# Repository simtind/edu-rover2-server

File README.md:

# EduROV server package

This package contains a server for use with the [circuit boards](https://github.com/simtind/edu-rover2-pcb) and [PC client](https://github.com/simtind/edu-rover2-client) from the pyedurov2 project, and the ROV chassis described on the EduROV webpage.

## Use
- To install, run ```pip install pyedurov2```.
  - If you got the warning ```The script normalizer is installed in * which is not on PATH.```, call ```source ~/.profile```.
- To run the server, run ```pyedurov2```.
- To start the server at boot, run ```pyedurov2 --runatstartup```.
- See ```pyedurov2 --help``` foor more options.

## Building package

Make sure the newest version of pip is installed: ```pip install --upgrade build```
Then from the edurov_server folder, run ```python -m build```

## Setting up Raspberry pi for EduROV

- Install Raspberry PI OS (32-bit), for example via [Raspberry Pi Imager](https://www.raspberrypi.com/software/)
- In SD card, add the file "ssh", it should be empty.
- Insert sd card to raspberry pi
- Connect via ssh to raspberrypi.local
- Via raspi-config:
  - Under Interface Options
    - Enable camera
    - Enable Serial Port:
      - We do not want a login shell to be available.
      - We do want the serial port hardware to obe enabled.
  - Allow the raspberry pi to restart and reconnect the ssh session.
- For pyedurov2 to run at startup, we'll need to install and run it as sudo.
- Install pyedurov2 with ```sudo pip install pyedurov2```
- Call ```sudo pyedurov2 --runatstartup --name=yourname``` to set server to start at boot with "yourname" as the advertising name.

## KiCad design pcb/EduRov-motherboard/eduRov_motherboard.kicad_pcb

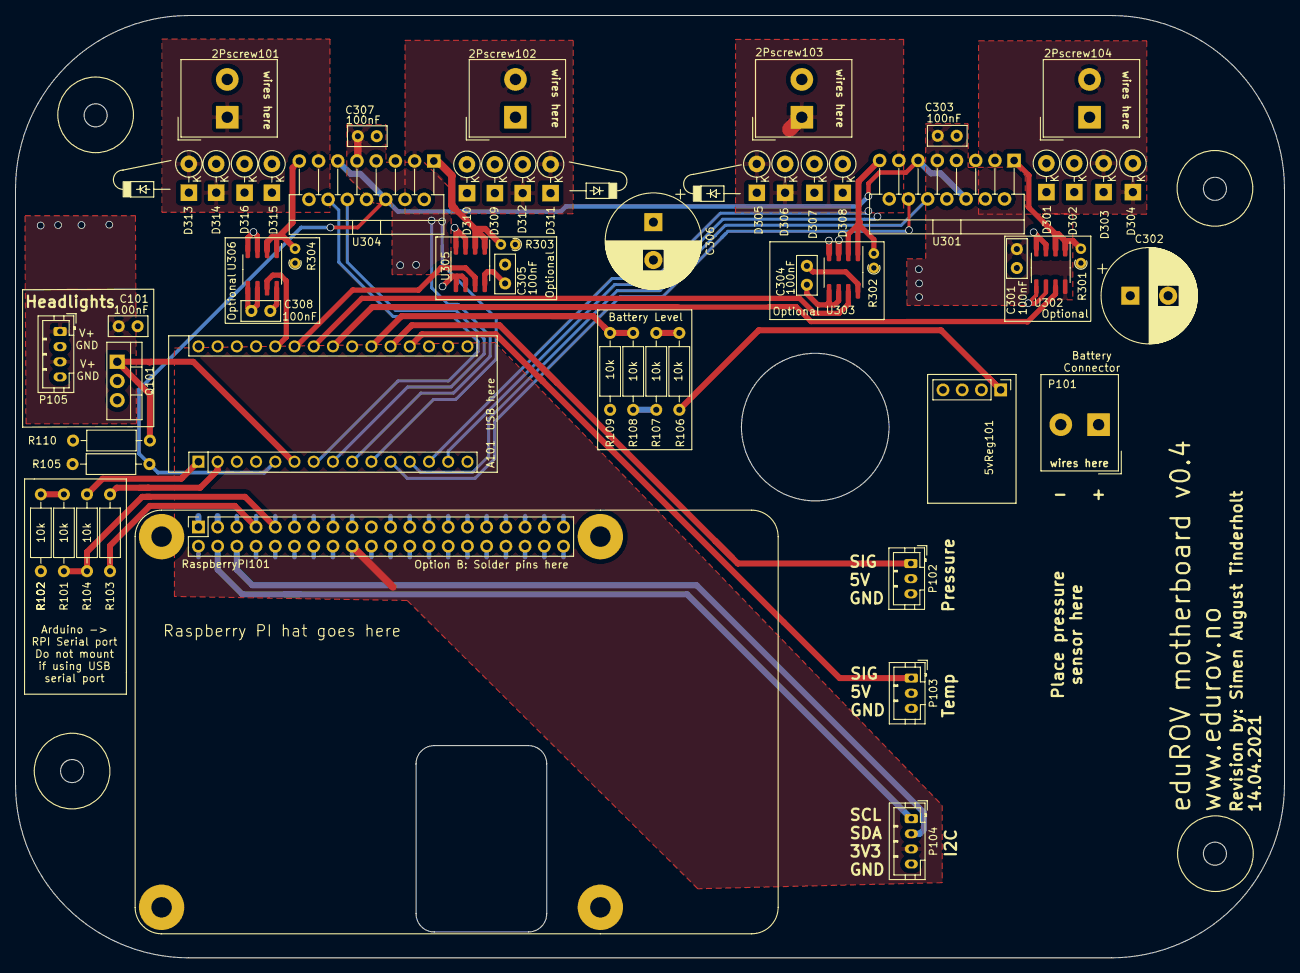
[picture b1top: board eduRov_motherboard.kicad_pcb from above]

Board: 4 copper layers, 167.7 x 124.6 mm, 58 parts (0 on the bottom side), 43 nets.

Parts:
2Pscrew101: Channel 1; Altech_AK300_1x02_P5.00mm_45-Degree
2Pscrew102: Channel 2; Altech_AK300_1x02_P5.00mm_45-Degree
2Pscrew103: Channel 3; Altech_AK300_1x02_P5.00mm_45-Degree
2Pscrew104: Channel 4; Altech_AK300_1x02_P5.00mm_45-Degree
5vReg101: Conn_01x04; PinHeader_1x04_P2.54mm_Vertical
A101: Arduino_Nano_v3.x; Arduino_Nano
C101, C301, C303, C304, C305, C307, C308: 100nF; C_Disc_D5.0mm_W2.5mm_P2.50mm
C302, C306: 470uF; CP_Radial_D12.5mm_P5.00mm
D301, D302, D303, D304, D305, D306, D307, D308, D309, D310, D311, D312, D313, D314, D315, D316: D; D_DO-41_SOD81_P3.81mm_Vertical_KathodeUp
P101: Battery connector; Altech_AK300_1x02_P5.00mm_45-Degree
P102, P103: Ext press; JST_PH_B3B-PH-K_1x03_P2.00mm_Vertical
P104: Ext press; JST_PH_B4B-PH-K_1x04_P2.00mm_Vertical
P105: Ch LED; JST_PH_B4B-PH-K_1x04_P2.00mm_Vertical
Q101: IRL540NPBF; TO-220-3_Vertical
R101, R102, R103, R104, R105, R106, R107, R108, R109, R110: 10k; R_Axial_DIN0207_L6.3mm_D2.5mm_P10.16mm_Horizontal
R301, R302, R303, R304: 0; R_Axial_DIN0204_L3.6mm_D1.6mm_P1.90mm_Vertical
RaspberryPI101: Raspberry_Pi_2_3; RaspBerry_PI
U301, U304: L298HN; TO-220-15_P2.54x2.54mm_StaggerOdd_Lead4.58mm_Vertical
U302, U303, U305, U306: ACS723xLCTR-05AB; SOIC-8_3.9x4.9mm_P1.27mm

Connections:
+3V3: A101.17, P104.3, RaspberryPI101.1, RaspberryPI101.17
+5V: 5vReg101.4, A101.27, C301.2, C303.2, C304.2, C305.2, C307.2, C308.2, P102.2, P103.2, RaspberryPI101.2, RaspberryPI101.4, U301.9, U302.8, U303.8, U304.9, U305.8, U306.8
+Bat: 5vReg101.1, C101.1, C302.1, C306.1, D301.1, D303.1, D305.1, D307.1, D309.1, D311.1, D313.1, D315.1, P101.1, P105.1, P105.3, R106.2, U301.4, U304.4
-Batt: 5vReg101.2, 5vReg101.3, A101.4, A101.29, C101.2, C301.1, C302.2, C303.1, C304.1, C305.1, C306.2, C307.1, C308.1, D302.2, D304.2, D306.2, D308.2, D310.2, D312.2, D314.2, D316.2, P101.2, P102.3, P103.3, P104.4, Q101.3, R102.1, R105.1, R109.1, R110.1, R301.1, R302.1, R303.1, R304.1, RaspberryPI101.6, RaspberryPI101.9, RaspberryPI101.14, RaspberryPI101.20, RaspberryPI101.25, RaspberryPI101.30, RaspberryPI101.34, RaspberryPI101.39, U301.8, U302.3, U302.4, U302.5, U302.6, U303.3, U303.4, U303.5, U303.6, U304.8, U305.3, U305.4, U305.5, U305.6, U306.3, U306.4, U306.5, U306.6
/Mot1+: 2Pscrew101.2, D315.2, D316.1, U304.14
/Mot1-: 2Pscrew101.1, D313.2, D314.1, U304.13
/Mot2+: 2Pscrew102.2, D311.2, D312.1, U304.3
/Mot2-: 2Pscrew102.1, D309.2, D310.1, U304.2
/Mot3+: 2Pscrew103.2, D307.2, D308.1, U301.14
/Mot3-: 2Pscrew103.1, D305.2, D306.1, U301.13
/Mot4+: 2Pscrew104.2, D303.2, D304.1, U301.3
/Mot4-: 2Pscrew104.1, D301.2, D302.1, U301.2
/MotorController1/IA: R303.2, U304.1, U305.1, U305.2
/MotorController1/IB: R304.2, U304.15, U306.1, U306.2
/MotorController2/IA: R301.2, U301.1, U302.1, U302.2
/MotorController2/IB: R302.2, U301.15, U303.1, U303.2
BattMonitor: A101.21, R108.1, R109.2
IO1A: A101.8, U304.10
IO1B: A101.7, U304.12
IO2A: A101.10, U304.5
IO2B: A101.9, U304.7
IO3A: A101.12, U301.10
IO3B: A101.11, U301.12
IO4A: A101.14, U301.5
IO4B: A101.13, U301.7
IOEN: A101.5, R105.2, U301.6, U301.11, U304.6, U304.11
IO_LED: A101.6, Q101.1, R110.2
LED-: P105.2, P105.4, Q101.2
unnamed: A101.1, R104.2
unnamed: A101.2, R103.1
unnamed: R101.1, R102.2
unnamed: R101.2, R104.1, RaspberryPI101.10
unnamed: R103.2, RaspberryPI101.8
unnamed: R106.1, R107.2
unnamed: R107.1, R108.2
PressMonitor: A101.20, P102.1
SCL: P104.1, RaspberryPI101.3
SDA: P104.2, RaspberryPI101.5
Sense1: A101.26, U306.7
Sense2: A101.25, U305.7
Sense3: A101.24, U303.7
Sense4: A101.23, U302.7
TempMonitor: A101.19, P103.1

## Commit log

2021-06-15 Use L298 motor driver
2021-08-11 Make repo server-only
2021-08-11 Rename main folder to make it legal
2021-08-11 Update gitignore.
2021-08-11 Fix file inclusion
2021-08-11 Rename source folder.
2021-09-12 Updates fromo raspberry pi.
2021-09-12 v0.0.2
2021-09-12 Fix python package command name.
2021-09-12 Fix package name
2021-09-12 Update version
2021-09-12 Updates from testing
2021-09-12 Set default loog level to something more palatable
2021-09-12 Fix setup.cfg and remove unused files.
2021-09-19 Add advertising server and remove web client.
2021-09-19 Remove build artifacts from git repo.
2021-09-19 Updates fom testing
2021-09-30 Add start-at-boot function to pyedurov2.
2021-09-30 Fix pyedurov2 service to run as default user.
2021-09-30 Use setup.py instead of setup.cfg.
2021-09-30 Make sure we're always using python3 in build script.
2021-09-30 Try without setuptools
2021-09-30 Clean up dependencies so we don't need to install the world when building release.
2021-09-30 Fix syntax
2021-09-30 Install the wheel
2021-09-30 Fix file inclusion in package.
2021-09-30 Allow user dir to exist when setting up startup at boot
2021-09-30 Move setup_startup function to system module.
2021-09-30 Allow pyedurov2 to be run as a module.
2021-09-30 Fix auto-startup
2021-11-07 Update pipy urls.
2021-11-07 Initial changes for custom name advertising.
2021-11-07 Handle advertising name in setup_startup function.
2021-11-07 Add advertising name to service template.
2021-11-07 Add custom name handling to advertising server.
2021-11-07 Remove old build files from repository
2021-11-07 Documentation updates
2021-11-07 Fix missing msg variable in wait_until_available function.
2021-11-07 Update version.
